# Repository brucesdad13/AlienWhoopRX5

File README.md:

# AlienWhoopRx

# AlienWhoopRx Features :alien:
AlienWhoop receiver 2.4GHz transceiver based on XN297LBW (code name AlienWhoop RX-5). Intended for SHORT RANGE flights around the house or yard. Limited penetration.

# Order PCB
https://oshpark.com/shared_projects/jJTTCoE2

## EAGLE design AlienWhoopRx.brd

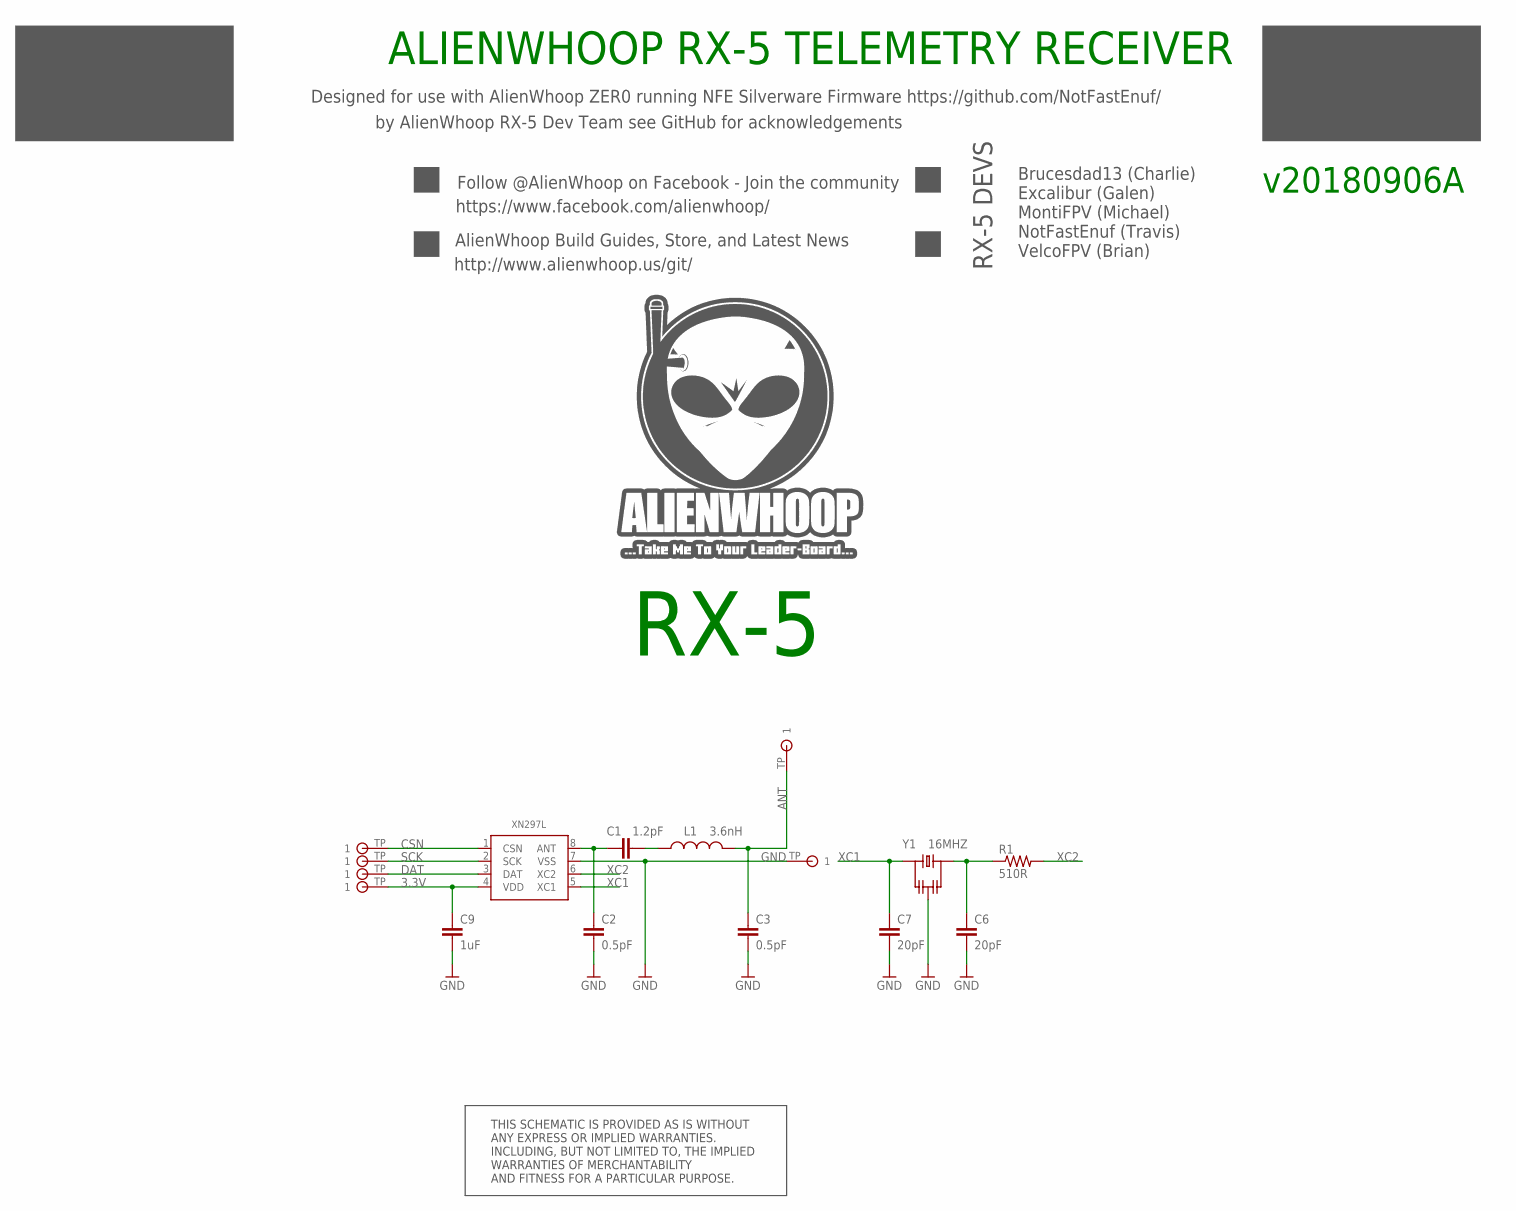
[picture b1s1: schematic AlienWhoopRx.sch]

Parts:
3.3V2: TESTPAD
C1: 1.2pF; 0402; PARTNO 0402YA1R2CAT2A
C2, C3: 0.5pF; 0402; PARTNO VJ0402A0R5BXJCW1BC
C6, C7: 20pF; 0402; PARTNO GJM1555C1H200FB01D
C9: 1uF; 0402; PARTNO GRM155C71A105KE11D
GND23: TESTPAD
L1: 3.6nH; 0402; PARTNO MHQ1005P3N6ST000
R1: 510R; 0402; PARTNO CR0402-FX-5100GLF
SPI_CS: TESTPAD
U1: XN297L; SOP8L; PARTNO XN297LBW
U$6, U$13, U$14: TESTPAD
Y1: 16MHZ; ECS-160-20-33-CKM-TR; PARTNO ECS-160-20-33-CKM-TR

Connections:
3.3V: 3.3V2.TP, C9.1, U1.4 (VDD)
ANT: C3.1, L1.2, U$6.TP
ANT_CAP: C1.2, L1.1
ANT_OUT: C1.1, C2.1, U1.8 (ANT)
CSN: SPI_CS.TP, U1.1 (CSN)
DAT: U1.3 (DAT), U$14.TP
GND: C2.2, C3.2, C6.2, C7.2, C9.2, GND23.TP, U1.7 (VSS), Y1.2, Y1.4 (2)
SCK: U1.2 (SCK), U$13.TP
XC1: C7.1, U1.5 (XC1), Y1.1
XC2: R1.2, U1.6 (XC2)
XC2R: C6.1, R1.1, Y1.3

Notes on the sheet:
Designed for use with AlienWhoop ZER0 running NFE Silverware Firmware https://github.com/NotFastEnuf/
https://www.facebook.com/alienwhoop/
Follow @AlienWhoop on Facebook - Join the community
by AlienWhoop RX-5 Dev Team see GitHub for acknowledgements
http://www.alienwhoop.us/git/
AlienWhoop Build Guides, Store, and Latest News
ALIENWHOOP RX-5 TELEMETRY RECEIVER
v20180906A
THIS SCHEMATIC IS PROVIDED AS IS WITHOUT ANY EXPRESS OR IMPLIED WARRANTIES. INCLUDING, BUT NOT LIMITED TO, THE IMPLIED WARRANTIES OF MERCHANTABILITY AND FITNESS FOR A PARTICULAR PURPOSE.
RX-5
Brucesdad13 (Charlie) Excalibur (Galen) MontiFPV (Michael) NotFastEnuf (Travis) VelcoFPV (Brian)
RX-5 DEVS

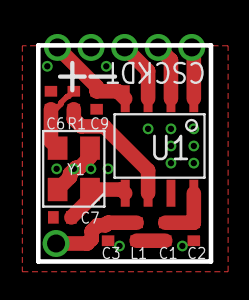
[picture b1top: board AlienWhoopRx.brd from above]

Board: 2 copper layers, 9.6 x 12.0 mm, 16 parts (0 on the bottom side), 11 nets.

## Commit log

2018-08-28 Initial commit of AlienWhoop RX-5 2.4GHz transceiver based on XN297LBW
2018-09-07 Shrunk overall dimensions. Second draft as ordered from OSH Park on 2018-09-06
2018-09-07 Updated with latest settings

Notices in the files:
parts and their libraries:
AlienWhoop: License: CC BY SA
alienflight: Released under the Creative Commons
Attribution Share-Alike 4.0 License
http://creativecommons.org/licenses/by-sa/4.0
